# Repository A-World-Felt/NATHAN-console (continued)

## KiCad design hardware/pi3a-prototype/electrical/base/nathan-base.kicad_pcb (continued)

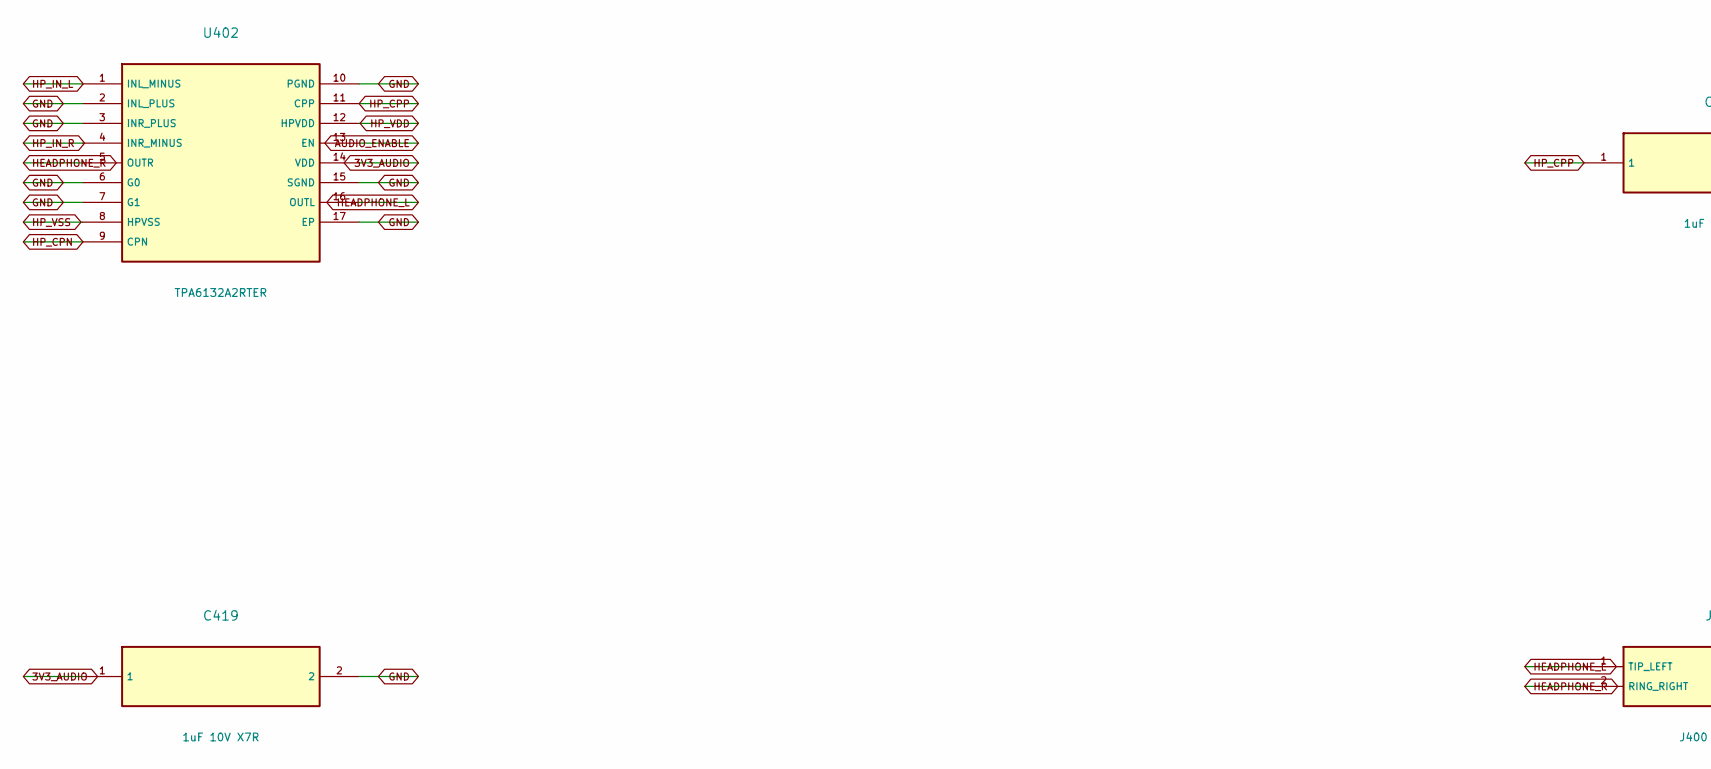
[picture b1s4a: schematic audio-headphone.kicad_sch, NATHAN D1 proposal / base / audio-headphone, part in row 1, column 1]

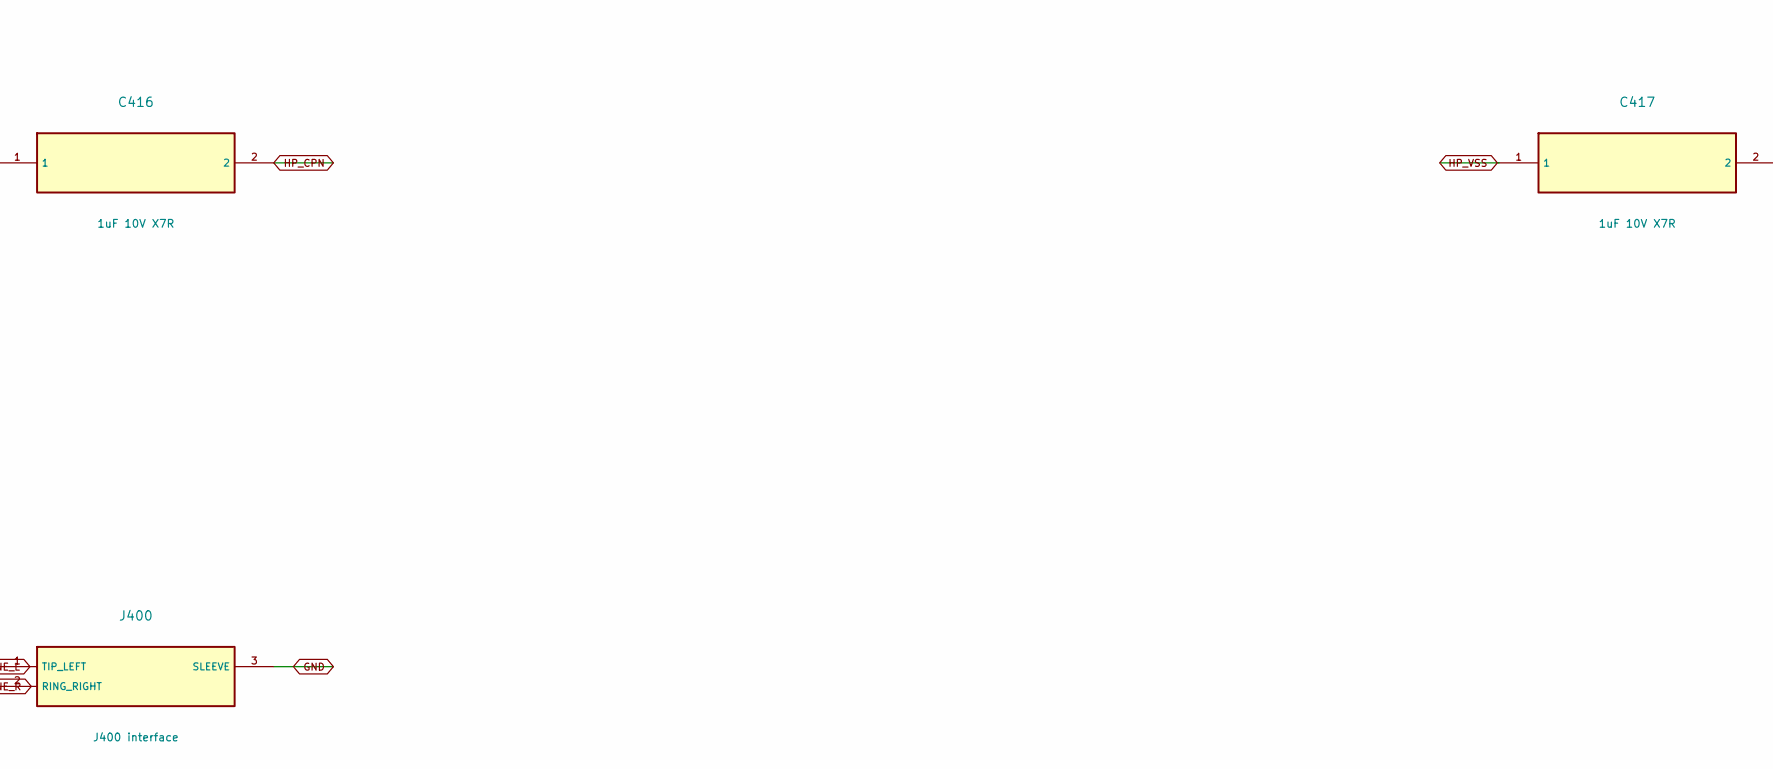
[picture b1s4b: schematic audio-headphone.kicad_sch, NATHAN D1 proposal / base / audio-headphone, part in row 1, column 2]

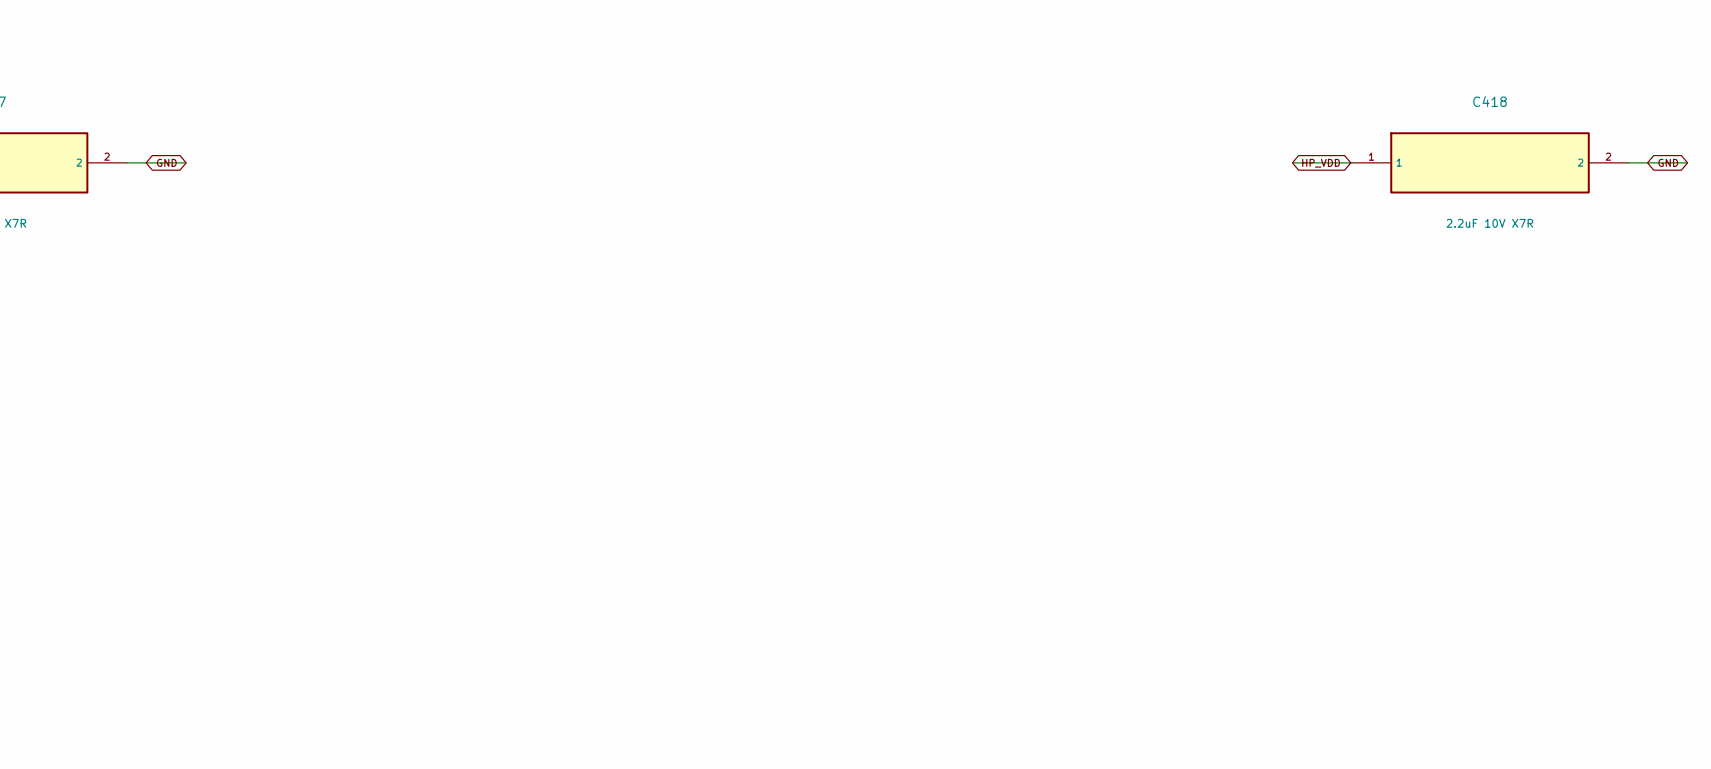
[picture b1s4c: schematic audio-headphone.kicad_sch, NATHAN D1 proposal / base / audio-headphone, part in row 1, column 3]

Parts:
C416, C417, C419: 1uF 10V X7R; C_0603_1608Metric
C418: 2.2uF 10V X7R; C_0603_1608Metric
J400: J400 interface; JST_PH_B3B-PH-K_1x03_P2.00mm_Vertical
U402: TPA6132A2RTER; WQFN-16-1EP_3x3mm_P0.5mm_EP1.6x1.6mm

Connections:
3V3_AUDIO: C419.1, U402.14 (VDD); also elsewhere on the board
AUDIO_ENABLE: U402.13 (EN); also elsewhere on the board
GND: C417.2, C418.2, C419.2, J400.3 (SLEEVE), U402.2 (INL_PLUS), U402.3 (INR_PLUS), U402.6 (G0), U402.7 (G1), U402.10 (PGND), U402.15 (SGND), U402.17 (EP); also elsewhere on the board
HEADPHONE_L: J400.1 (TIP_LEFT), U402.16 (OUTL)
HEADPHONE_R: J400.2 (RING_RIGHT), U402.5 (OUTR)
HP_CPN: C416.2, U402.9 (CPN)
HP_CPP: C416.1, U402.11 (CPP)
HP_IN_L: U402.1 (INL_MINUS); also elsewhere on the board
HP_IN_R: U402.4 (INR_MINUS); also elsewhere on the board
HP_VDD: C418.1, U402.12 (HPVDD)
HP_VSS: C417.1, U402.8 (HPVSS)

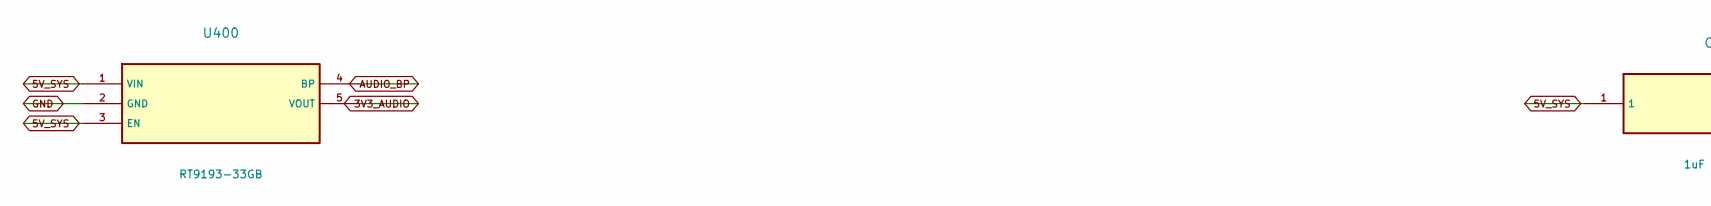
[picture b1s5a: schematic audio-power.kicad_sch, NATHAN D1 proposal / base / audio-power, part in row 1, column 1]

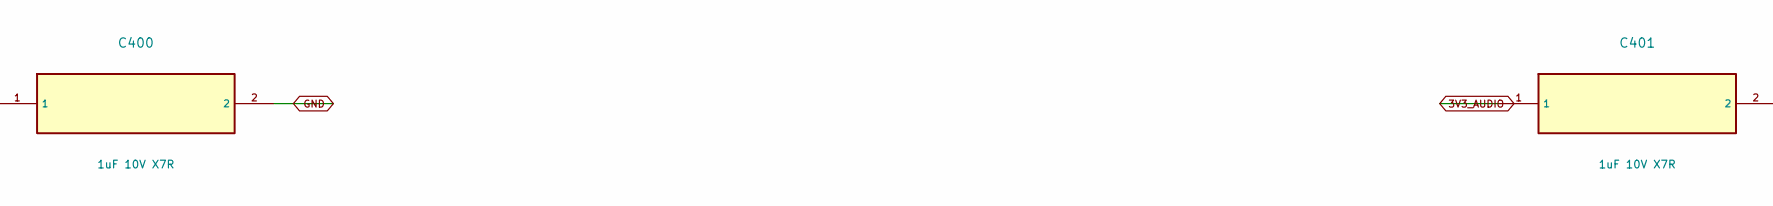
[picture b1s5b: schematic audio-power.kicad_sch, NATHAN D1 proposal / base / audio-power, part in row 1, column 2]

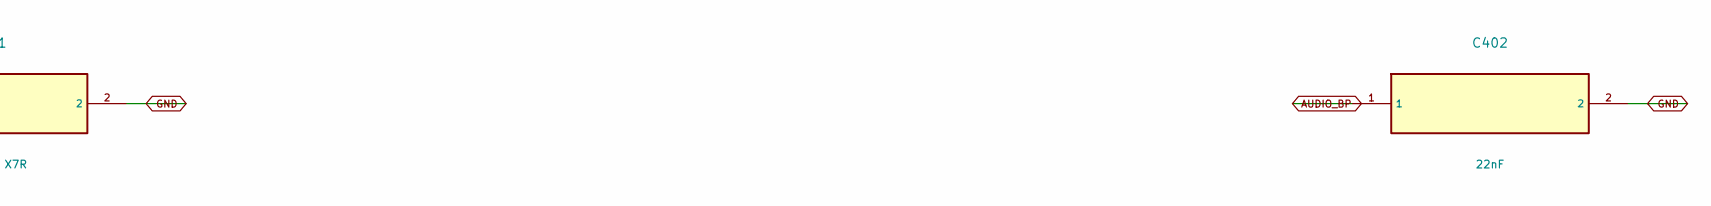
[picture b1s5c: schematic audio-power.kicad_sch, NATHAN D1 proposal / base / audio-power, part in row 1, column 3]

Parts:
C400, C401: 1uF 10V X7R; C_0603_1608Metric
C402: 22nF; C_0603_1608Metric
U400: RT9193-33GB; SOT-23-5

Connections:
3V3_AUDIO: C401.1, U400.5 (VOUT); also elsewhere on the board
5V_SYS: C400.1, U400.1 (VIN), U400.3 (EN); also elsewhere on the board
AUDIO_BP: C402.1, U400.4 (BP)
GND: C400.2, C401.2, C402.2, U400.2 (GND); also elsewhere on the board

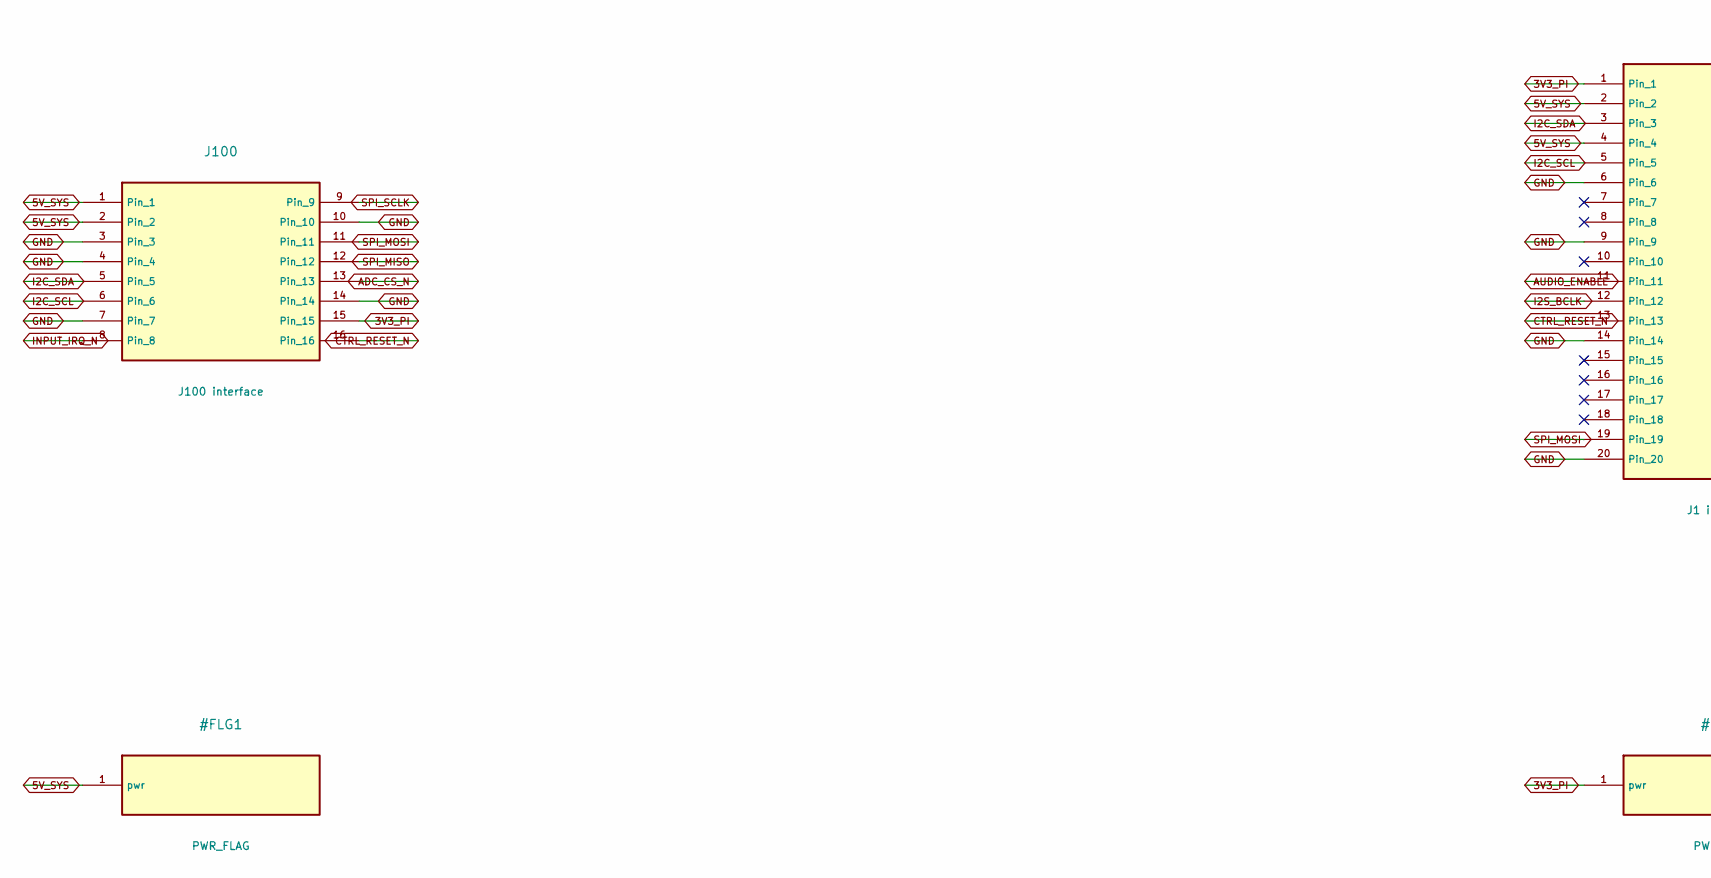
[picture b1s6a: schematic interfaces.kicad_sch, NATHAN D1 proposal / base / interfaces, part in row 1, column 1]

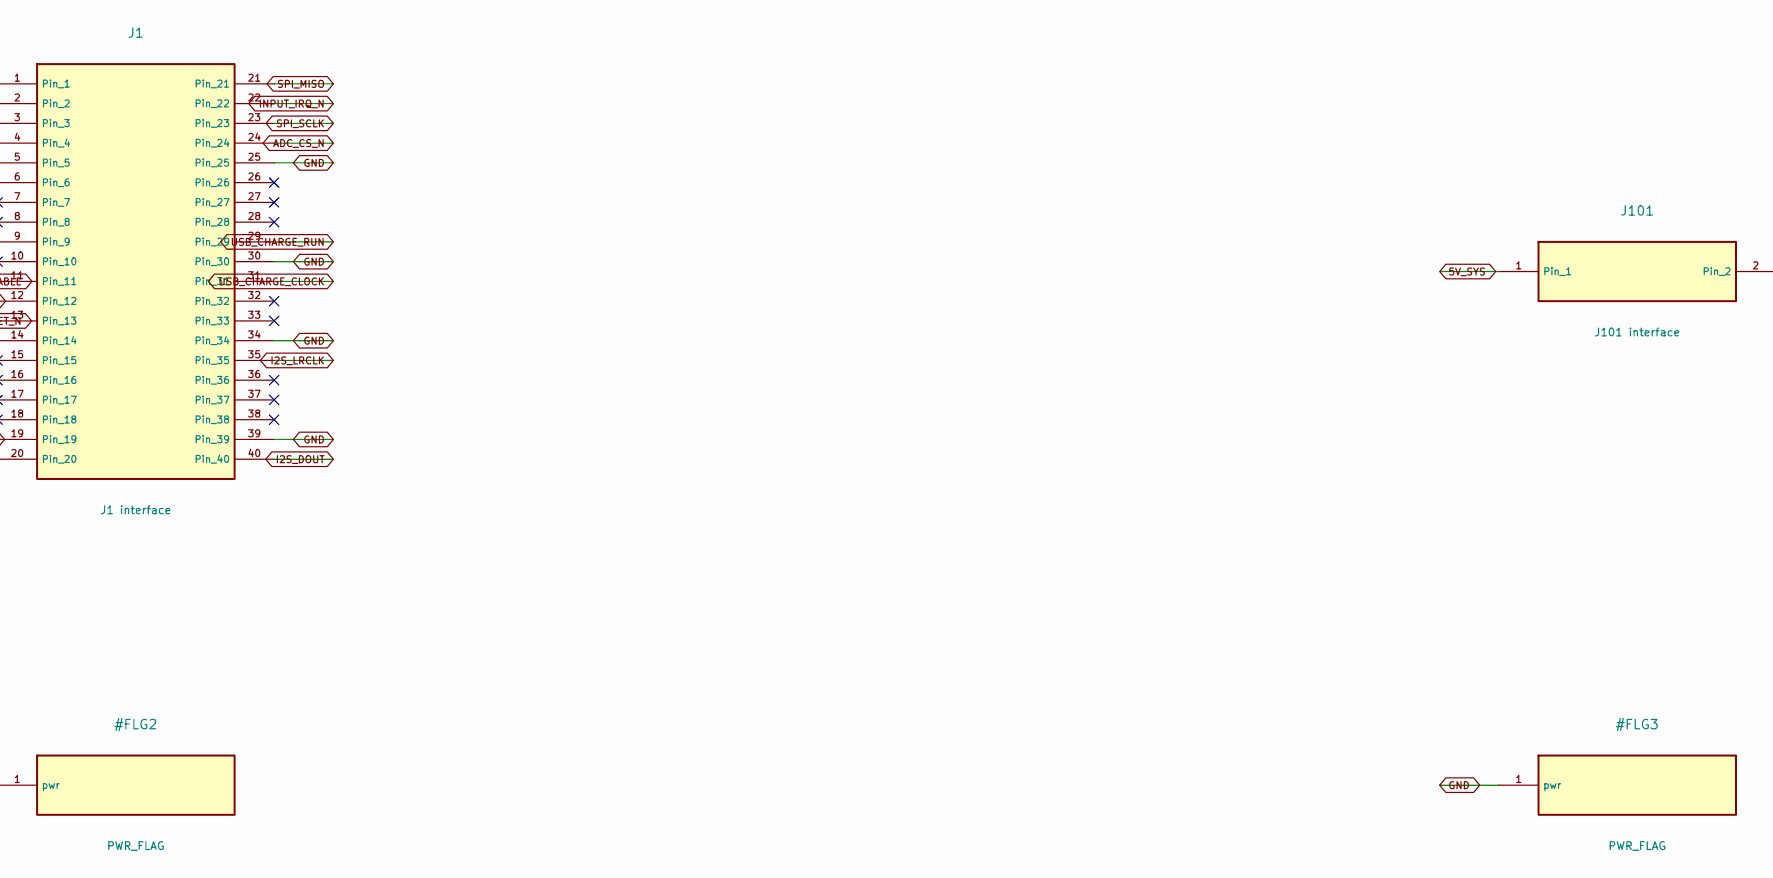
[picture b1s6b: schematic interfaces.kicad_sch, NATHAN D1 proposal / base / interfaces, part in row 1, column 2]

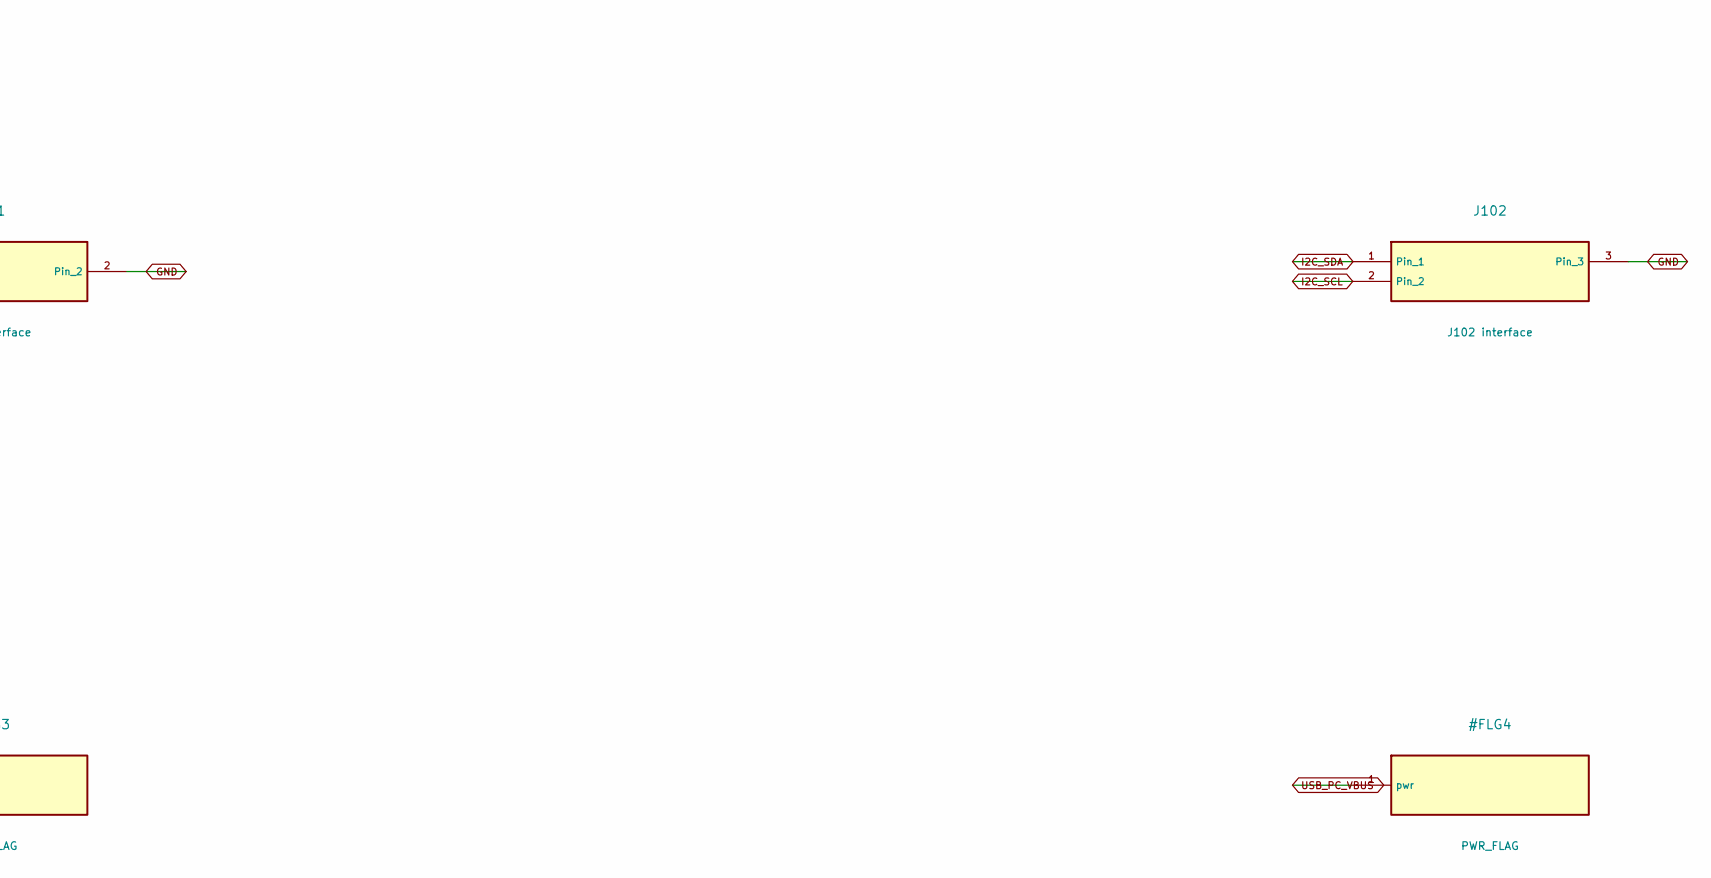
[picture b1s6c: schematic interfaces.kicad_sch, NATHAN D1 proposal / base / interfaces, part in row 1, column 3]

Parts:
J1: J1 interface; IDC-Header_2x20_P2.54mm_Vertical
J100: J100 interface; IDC-Header_2x08_P2.54mm_Vertical
J101: J101 interface; Power_Pigtail_2Pad
J102: J102 interface; JST_PH_B3B-PH-K_1x03_P2.00mm_Vertical

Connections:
3V3_PI: J1.1, J100.15; also elsewhere on the board
5V_SYS: J1.2, J1.4, J100.1, J100.2, J101.1; also elsewhere on the board
ADC_CS_N: J1.24, J100.13
AUDIO_ENABLE: J1.11; also elsewhere on the board
CTRL_RESET_N: J1.13, J100.16
GND: J1.6, J1.9, J1.14, J1.20, J1.25, J1.30, J1.34, J1.39, J100.3, J100.4, J100.7, J100.10, J100.14, J101.2, J102.3; also elsewhere on the board
I2C_SCL: J1.5, J100.6, J102.2
I2C_SDA: J1.3, J100.5, J102.1
I2S_BCLK: J1.12; also elsewhere on the board
I2S_DOUT: J1.40; also elsewhere on the board
I2S_LRCLK: J1.35; also elsewhere on the board
INPUT_IRQ_N: J1.22, J100.8
SPI_MISO: J1.21, J100.12
SPI_MOSI: J1.19, J100.11
SPI_SCLK: J1.23, J100.9
USB_CHARGE_CLOCK: J1.31; also elsewhere on the board
USB_CHARGE_RUN: J1.29; also elsewhere on the board

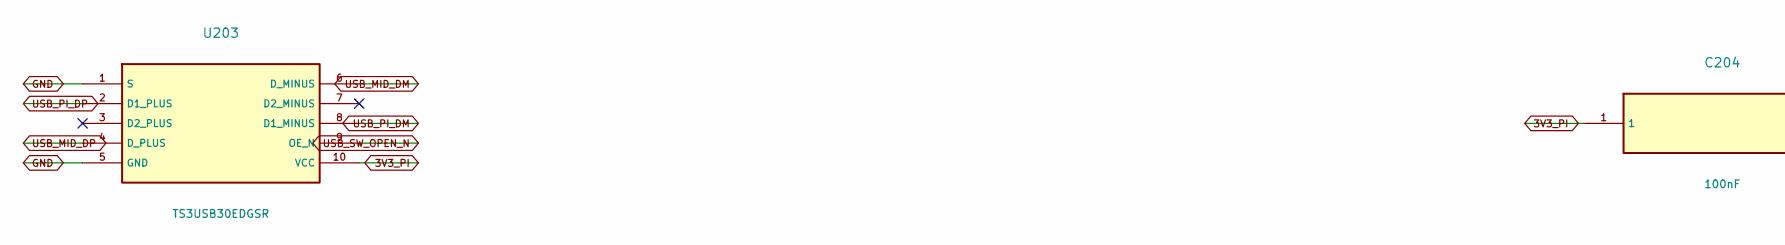
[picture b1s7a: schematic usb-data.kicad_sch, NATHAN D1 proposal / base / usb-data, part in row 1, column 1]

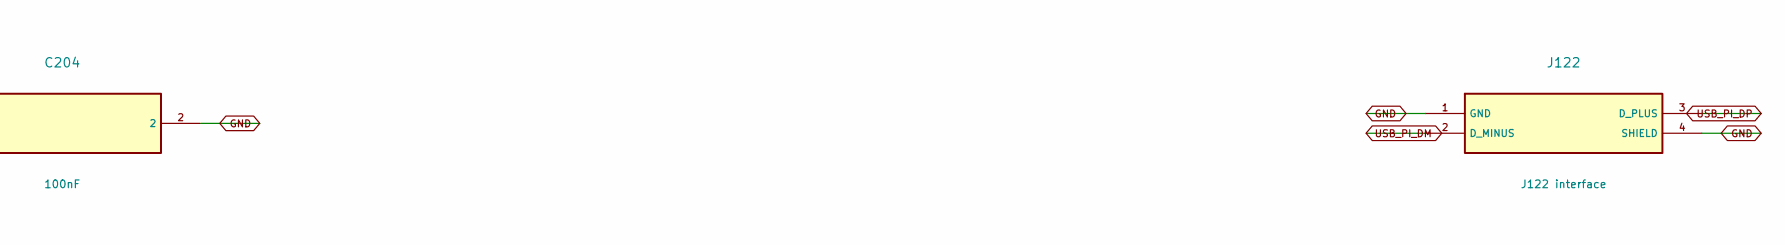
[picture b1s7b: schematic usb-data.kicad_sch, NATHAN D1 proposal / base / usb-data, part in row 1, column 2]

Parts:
C204: 100nF; C_0603_1608Metric
J122: J122 interface; USB_Data_Pigtail_4Pad
U203: TS3USB30EDGSR; VSSOP-10_3x3mm_P0.5mm

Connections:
3V3_PI: C204.1, U203.10 (VCC); also elsewhere on the board
GND: C204.2, J122.1 (GND), J122.4 (SHIELD), U203.1 (S), U203.5 (GND); also elsewhere on the board
USB_MID_DM: U203.6 (D_MINUS); also elsewhere on the board
USB_MID_DP: U203.4 (D_PLUS); also elsewhere on the board
USB_PI_DM: J122.2 (D_MINUS), U203.8 (D1_MINUS)
USB_PI_DP: J122.3 (D_PLUS), U203.2 (D1_PLUS)
USB_SW_OPEN_N: U203.9 (OE_N); also elsewhere on the board
